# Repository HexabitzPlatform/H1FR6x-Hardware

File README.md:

# H1FR6x-Hardware

Hexabitz TESEO-LIV4F GNSS Module Hardware Design

Redesign using the STM32G0B1CEU6 MCU and Teseo-LIV4F. Review the previous design for errors and correct them. Use the X-NUCLEO-LIV4A1 design as a reference.

This design must use two hexagons with a 4-layer PCB stack-up.

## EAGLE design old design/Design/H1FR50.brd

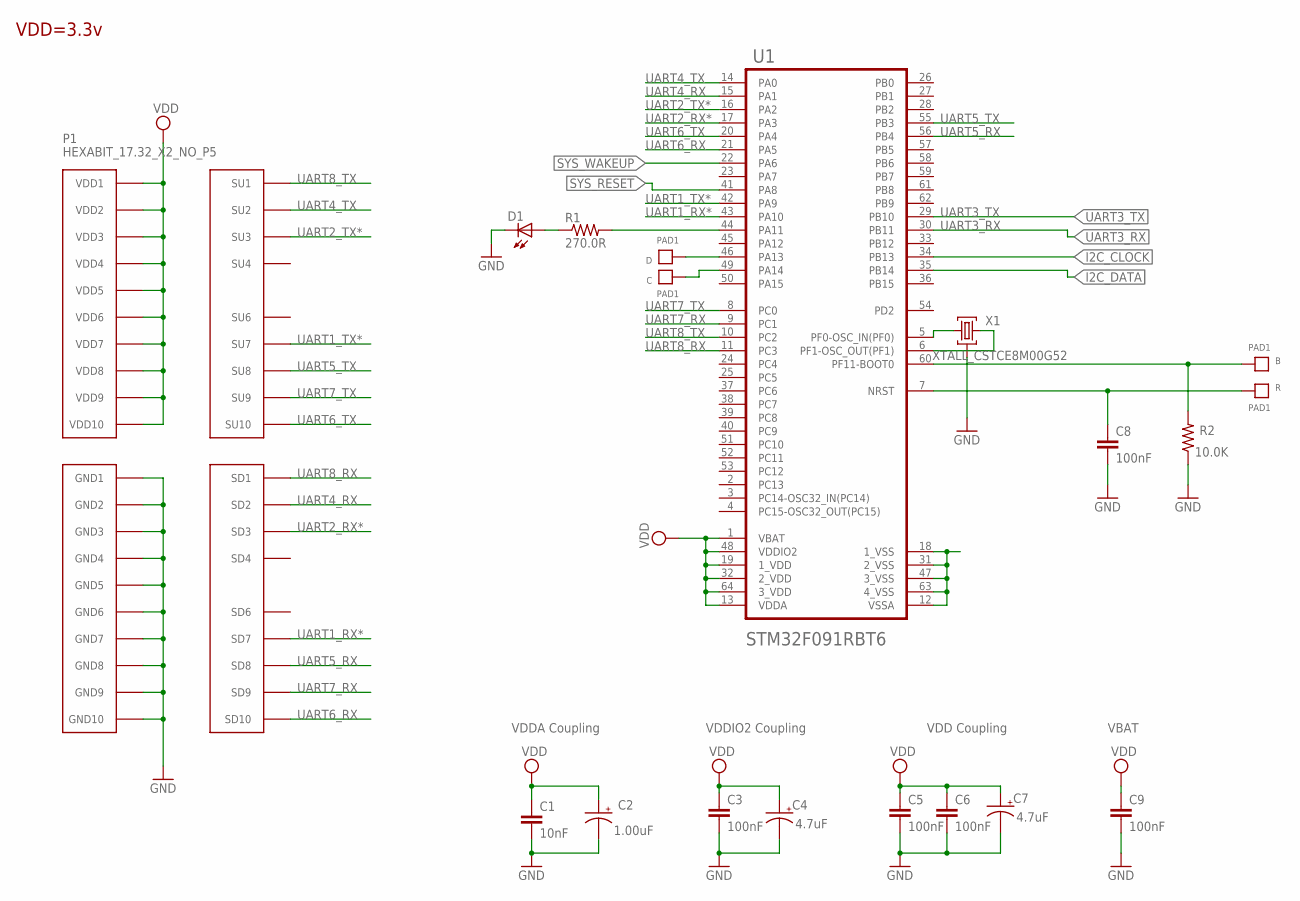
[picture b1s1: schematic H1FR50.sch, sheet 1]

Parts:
B: PAD1
C: PAD1
C1: 10nF; C-0603; TOLERANCE 10%; VOLTAGE_RATING 50V; MPN C0603C103K5RACTU
C2: 1.00uF; C-0805-POL; TOLERANCE 10%; VOLTAGE_RATING 16V; MPN CC0805KKX7R7BB105
C3, C6, C8: 100nF; C-0603; TOLERANCE 10%; VOLTAGE_RATING 10V; MPN C0603C104K8RACTU
C4, C7: 4.7uF; C-0805-POL; TOLERANCE 10%; VOLTAGE_RATING 25V; MPN GRM21BC81E475KA12L
C5: 100nF; C-0603; TOLERANCE 10%; VOLTAGE_RATING 10; MPN C0603C104K8RACTU
C9: 100nF; C-0603; TOLERANCE 10V; VOLTAGE_RATING 10%; MPN C0603C104K8RACTU
D: PAD1
D1: VLMS1300-GS08; MPN VLMS1300-GS08
P1: HEXABIT_17.32_X2_NO_P5
R: PAD1
R1: 270.0R; R-0603; TOLERANCE 1%; MPN RC0603FR-07270RL
R2: 10.0K; R-0603; TOLERANCE 5%; MPN RC0603JR-0710KL
U1: STM32F091RBT6STMICROELECTRONICS_STM32F091RBT6_0_1; STMICROELECTRONICS_STM32F091RBT6_1
X1: XTALL_CSTCE8M00G52

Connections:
B1: B.P$1, B.P$2, R2.2, U1.60 (PF11-BOOT0)
GND: C1.2, C2.2 (-), C3.2, C4.2 (-), C5.2, C6.2, C7.2 (-), C8.2, C9.2, D1.C, P1.PAD_PD11 (GND1), P1.PAD_PD12 (GND2), P1.PAD_PD13 (GND3), P1.PAD_PD14 (GND4), P1.PAD_PD15 (GND5), P1.PAD_PD16 (GND6), P1.PAD_PD17 (GND7), P1.PAD_PD18 (GND8), P1.PAD_PD19 (GND9), P1.PAD_PD20 (GND10), R2.1, U1.12 (VSSA), U1.18 (1_VSS), U1.31 (2_VSS), U1.47 (3_VSS), U1.63 (4_VSS), X1.P$2 (2); also elsewhere on the board
I2C_CLOCK: U1.34 (PB13); also elsewhere on the board
I2C_DATA: U1.35 (PB14); also elsewhere on the board
unnamed: D1.A, R1.1
unnamed: U1.5 (PF0-OSC_IN(PF0)), X1.P$1 (1)
unnamed: U1.6 (PF1-OSC_OUT(PF1)), X1.P$3 (3)
unnamed: D.P$1, D.P$2, U1.46 (PA13)
unnamed: C.P$1, C.P$2, U1.49 (PA14)
unnamed: R1.2, U1.44 (PA11)
R1: C8.1, R.P$1, R.P$2, U1.7 (NRST)
SYS_RESET: U1.41 (PA8); also elsewhere on the board
SYS_WAKEUP: U1.22 (PA6); also elsewhere on the board
UART1_RX*: P1.PAD_PD7 (SD7), U1.43 (PA10)
UART1_TX*: P1.PAD_PU7 (SU7), U1.42 (PA9)
UART2_RX*: P1.PAD_PD3 (SD3), U1.17 (PA3)
UART2_TX*: P1.PAD_PU3 (SU3), U1.16 (PA2)
UART3_RX: U1.30 (PB11); also elsewhere on the board
UART3_TX: U1.29 (PB10); also elsewhere on the board
UART4_RX: P1.PAD_PD2 (SD2), U1.15 (PA1)
UART4_TX: P1.PAD_PU2 (SU2), U1.14 (PA0)
UART5_RX: P1.PAD_PD8 (SD8), U1.56 (PB4)
UART5_TX: P1.PAD_PU8 (SU8), U1.55 (PB3)
UART6_RX: P1.PAD_PD10 (SD10), U1.21 (PA5)
UART6_TX: P1.PAD_PU10 (SU10), U1.20 (PA4)
UART7_RX: P1.PAD_PD9 (SD9), U1.9 (PC1)
UART7_TX: P1.PAD_PU9 (SU9), U1.8 (PC0)
UART8_RX: P1.PAD_PD1 (SD1), U1.11 (PC3)
UART8_TX: P1.PAD_PU1 (SU1), U1.10 (PC2)
VDD: C1.1, C2.1 (+), C3.1, C4.1 (+), C5.1, C6.1, C7.1 (+), C9.1, P1.PAD_PU11 (VDD1), P1.PAD_PU12 (VDD2), P1.PAD_PU13 (VDD3), P1.PAD_PU14 (VDD4), P1.PAD_PU15 (VDD5), P1.PAD_PU16 (VDD6), P1.PAD_PU17 (VDD7), P1.PAD_PU18 (VDD8), P1.PAD_PU19 (VDD9), P1.PAD_PU20 (VDD10), U1.1 (VBAT), U1.13 (VDDA), U1.19 (1_VDD), U1.32 (2_VDD), U1.48 (VDDIO2), U1.64 (3_VDD); also elsewhere on the board

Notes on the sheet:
VDDA Coupling
VDDIO2 Coupling
VDD Coupling
VBAT
VDD=3.3v

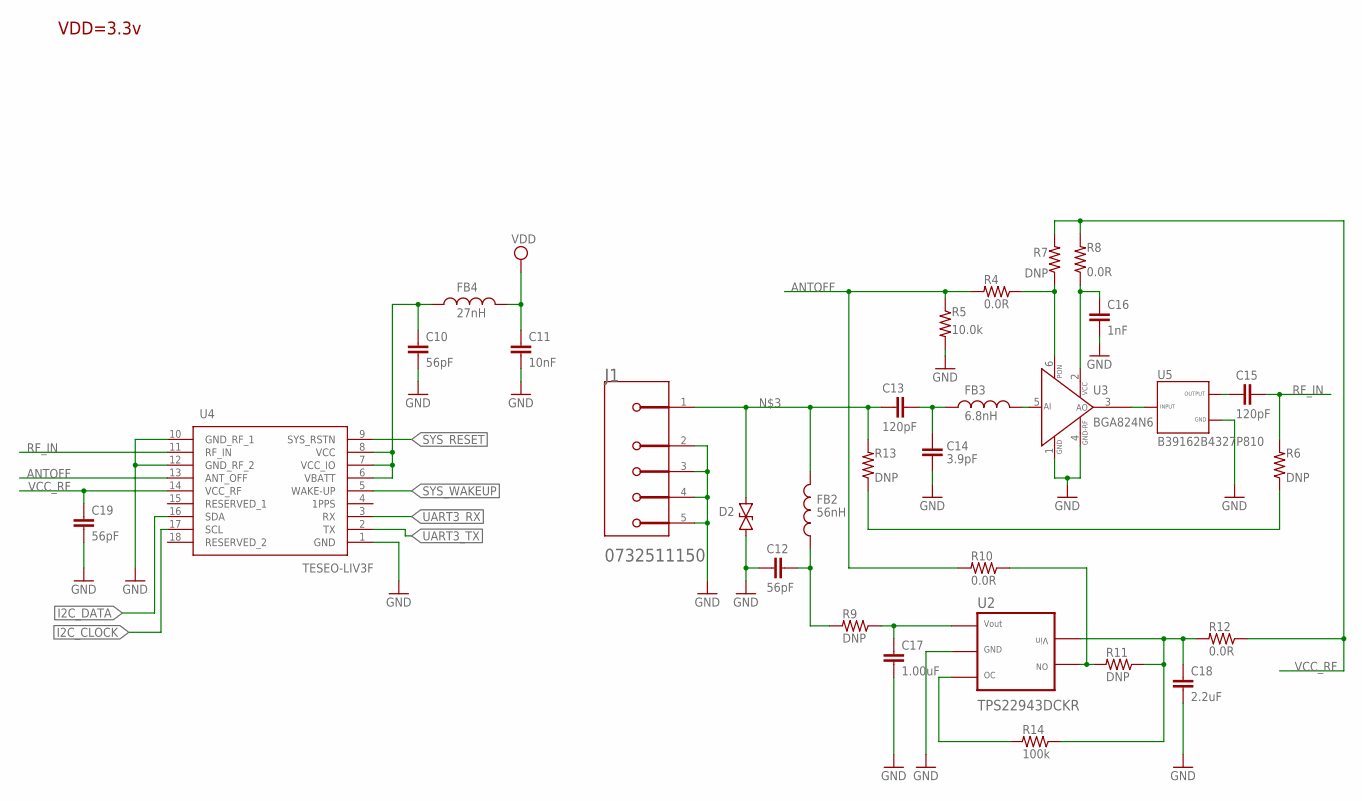
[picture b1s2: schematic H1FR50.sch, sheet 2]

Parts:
C10, C19: 56pF; C-0201; MPN GRM0335C1E560GA01D
C11: 10nF; C-0402; MPN CGA2B3X7R1H103K050BE
C12: 56pF; C-0402; MPN GRM1555C1H560JA01D
C13, C15: 120pF; C-0402; MPN GRM1555C1H121JA01D
C14: 3.9pF; C-0402; MPN GRM1555C1H3R9WA01D
C16: 1nF; C-0402; MPN GRM155R71H102KA01D
C17: 1.00uF; C-0402; MPN C0402C105K8PAC7411
C18: 2.2uF; C-0402; MPN C0402C225K7PACTU
D2: ESDARF02-1BU2CK; CAPC0201X13N
FB2: 56nH; FB-0402; MPN LQW15AN6N8G00D
FB3: 6.8nH; FB-0402; MPN 744784156A
FB4: 27nH; FB-0402; MPN LQG15HS27NJ02D
J1: MOLEX_INC_0732511150MOLEX_INC_0732511150_0_0; MOLEX_INC_0732511150_0
R4, R8, R10, R12: 0.0R; R-0402
R5: 10.0k; R-0402; TOLERANCE ±1%; MPN CRGCQ0402F10K
R6, R7, R9, R11, R13: DNP; R-0402
R14: 100k; R-0603; TOLERANCE ±1%; MPN AC0603FR-07100KL
U2: TPS22943DCKR; SOT65P210X110-5N
U3: BGA824N6
U4: TESEO-LIV3F; SON110P970X1010X230-18N
U5: B39162B4327P810; FIL_B39162B4327P810

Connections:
ANTOFF: R4.2, R5.1, R10.2, U4.13 (ANT_OFF)
ANT_IN: R6.1, R13.1
GND: C10.1, C11.1, C12.1, C14.1, C16.2, C17.2, C18.2, C19.1, D2.1, J1.2 (MNT_1), J1.3 (MNT_2), J1.4 (MNT_3), J1.5 (MNT_4), R5.2, U2.2 (GND), U3.1 (GND), U3.4 (GND-RF), U4.1 (GND), U4.10 (GND_RF_1), U4.12 (GND_RF_2), U5.2 (GND), U5.3 (GND), U5.5 (GND); also elsewhere on the board
I2C_CLOCK: U4.17 (SCL); also elsewhere on the board
I2C_DATA: U4.16 (SDA); also elsewhere on the board
unnamed: C13.2, C14.2, FB3.1
unnamed: R14.2, U2.3 (OC)
unnamed: C13.1, D2.2, FB2.2, J1.1, R13.2
unnamed: C12.2, FB2.1, R9.2
unnamed: FB3.2, U3.5 (AI)
unnamed: U3.3 (AO), U5.1 (INPUT)
unnamed: R4.1, R7.1, U3.6 (PON)
unnamed: C15.1, U5.4 (OUTPUT)
unnamed: C16.1, R8.1, U3.2 (VCC)
unnamed: C17.1, R9.1, U2.1 (VOUT)
unnamed: R10.1, R11.2, U2.4 (ON)
unnamed: C18.1, R11.1, R12.2, R14.1, U2.5 (VIN)
RF_IN: C15.2, R6.2, U4.11 (RF_IN)
SYS_RESET: U4.9 (SYS_RSTN); also elsewhere on the board
SYS_WAKEUP: U4.5 (WAKE-UP); also elsewhere on the board
UART3_RX: U4.3 (RX); also elsewhere on the board
UART3_TX: U4.2 (TX); also elsewhere on the board
VCC_RF: C19.2, R7.2, R8.2, R12.1, U4.14 (VCC_RF)
VCC_RF1: C10.2, FB4.1, U4.6 (VBATT), U4.7 (VCC_IO), U4.8 (VCC)
VDD: C11.2, FB4.2; also elsewhere on the board

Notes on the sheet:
VDD=3.3v

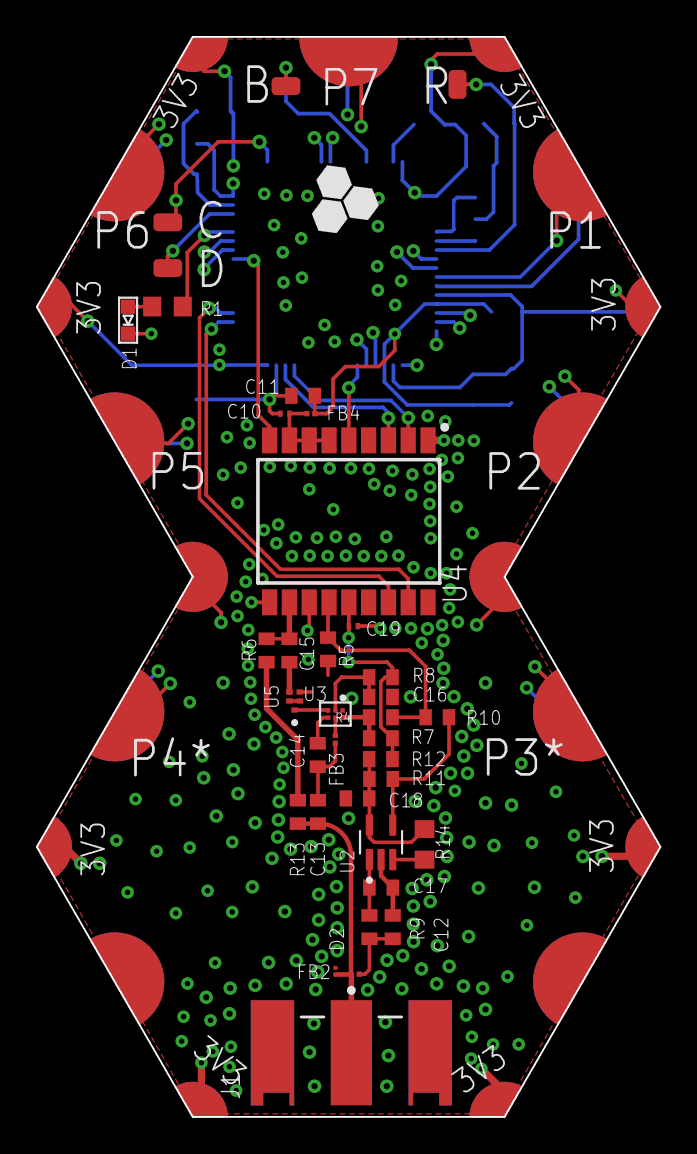
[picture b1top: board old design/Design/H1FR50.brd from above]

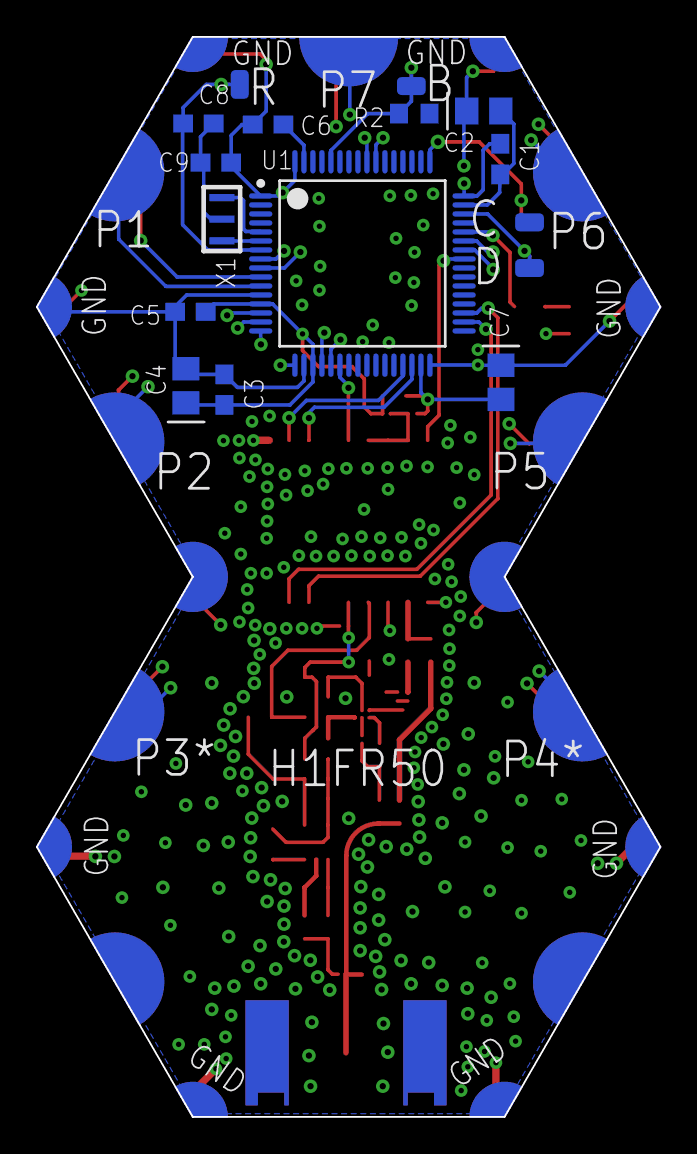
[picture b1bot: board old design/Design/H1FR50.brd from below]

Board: 4 copper layers, 34.6 x 60.0 mm, 49 parts (12 on the bottom side), 47 nets.

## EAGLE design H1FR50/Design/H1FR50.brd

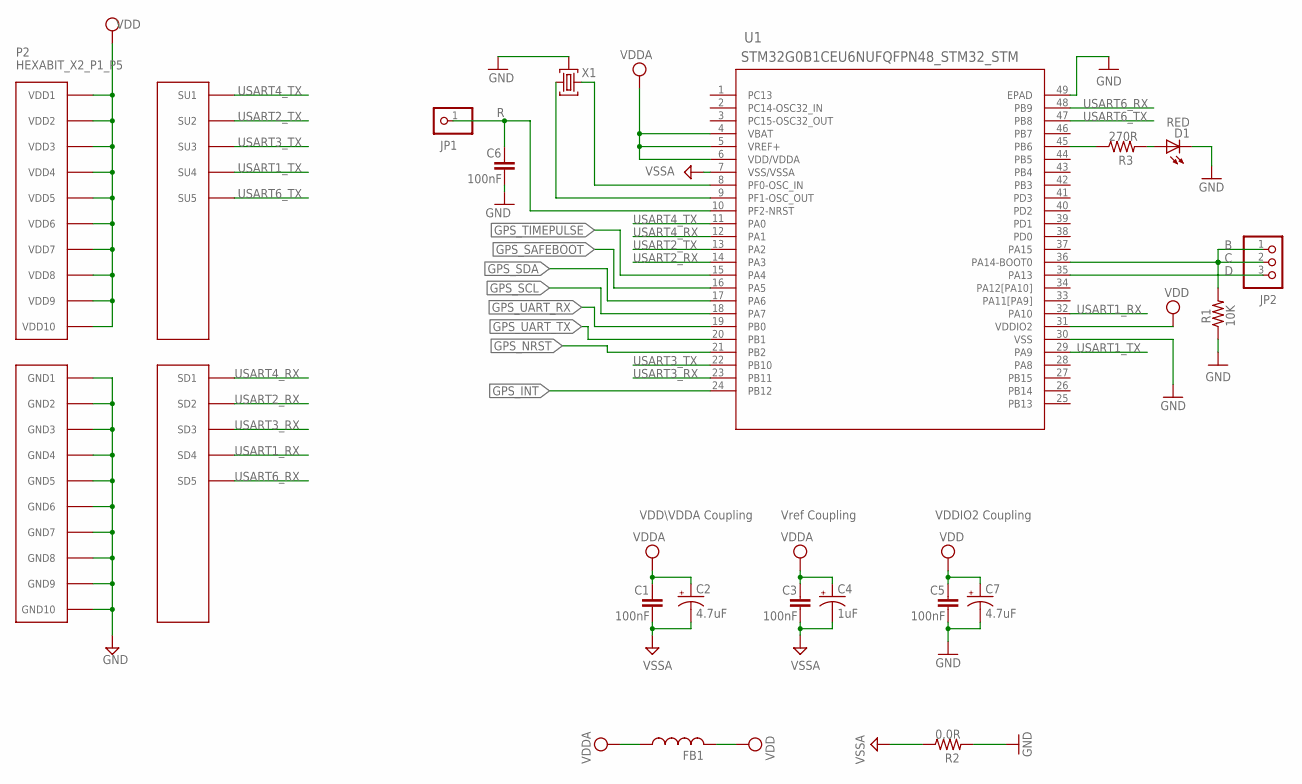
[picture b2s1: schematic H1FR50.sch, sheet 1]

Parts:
C1, C3, C5, C6: 100nF; C-0603
C2, C7: 4.7uF; C-0805-POL
C4: 1uF; C-0805-POL
D1: RED; VLMS1300-GS08
FB1: FB-0603
JP1: R; 1X01
JP2: PINHD-1X3; 1X03
P2: HEXABIT_X2_P1_P5; HEXABIT_17.32_X2_P1_P5
R1: 10K; R-0603
R2: 0.0R; R-0603
R3: 270R; R-0603
U1: STM32G0B1CEU6NUFQFPN48_STM32_STM; UFQFPN48_STM32_STM
X1: XTALL_CSTCE8M00G52

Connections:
C: JP2.1, JP2.2, R1.2, U1.36 (PA14-BOOT0)
D: JP2.3, U1.35 (PA13)
GND: C5.2, C6.2, C7.2 (-), D1.C, P2.PAD_PD11 (GND1), P2.PAD_PD12 (GND2), P2.PAD_PD13 (GND3), P2.PAD_PD14 (GND4), P2.PAD_PD15 (GND5), P2.PAD_PD16 (GND6), P2.PAD_PD17 (GND7), P2.PAD_PD18 (GND8), P2.PAD_PD19 (GND9), P2.PAD_PD20 (GND10), R1.1, R2.2, U1.30 (VSS), U1.49 (EPAD), X1.P$2 (2); also elsewhere on the board
GPS_INT: U1.24 (PB12); also elsewhere on the board
GPS_NRST: U1.21 (PB2); also elsewhere on the board
GPS_SAFEBOOT: U1.16 (PA5); also elsewhere on the board
GPS_SCL: U1.18 (PA7); also elsewhere on the board
GPS_SDA: U1.17 (PA6); also elsewhere on the board
GPS_TIMEPULSE: U1.15 (PA4); also elsewhere on the board
GPS_UART_RX: U1.19 (PB0); also elsewhere on the board
GPS_UART_TX: U1.20 (PB1); also elsewhere on the board
unnamed: D1.A, R3.2
unnamed: U1.8 (PF0-OSC_IN), X1.P$1 (1)
unnamed: U1.9 (PF1-OSC_OUT), X1.P$3 (3)
unnamed: C6.1, JP1.1, U1.10 (PF2-NRST)
unnamed: R3.1, U1.45 (PB6)
USART1_RX: P2.PAD_PD4 (SD4), U1.32 (PA10)
USART1_TX: P2.PAD_PU4 (SU4), U1.29 (PA9)
USART2_RX: P2.PAD_PD2 (SD2), U1.14 (PA3)
USART2_TX: P2.PAD_PU2 (SU2), U1.13 (PA2)
USART3_RX: P2.PAD_PD3 (SD3), U1.23 (PB11)
USART3_TX: P2.PAD_PU3 (SU3), U1.22 (PB10)
USART4_RX: P2.PAD_PD1 (SD1), U1.12 (PA1)
USART4_TX: P2.PAD_PU1 (SU1), U1.11 (PA0)
USART6_RX: P2.PAD_PD5 (SD5), U1.48 (PB9)
USART6_TX: P2.PAD_PU5 (SU5), U1.47 (PB8)
VDD: C5.1, C7.1 (+), FB1.2, P2.PAD_PU11 (VDD1), P2.PAD_PU12 (VDD2), P2.PAD_PU13 (VDD3), P2.PAD_PU14 (VDD4), P2.PAD_PU15 (VDD5), P2.PAD_PU16 (VDD6), P2.PAD_PU17 (VDD7), P2.PAD_PU18 (VDD8), P2.PAD_PU19 (VDD9), P2.PAD_PU20 (VDD10), U1.31 (VDDIO2); also elsewhere on the board
VDDA: C1.1, C2.1 (+), C3.1, C4.1 (+), FB1.1, U1.4 (VBAT), U1.5 (VREF+), U1.6 (VDD/VDDA)
VSSA: C1.2, C2.2 (-), C3.2, C4.2 (-), R2.1, U1.7 (VSS/VSSA)

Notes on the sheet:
Vref Coupling
VDDIO2 Coupling
VDD\VDDA Coupling

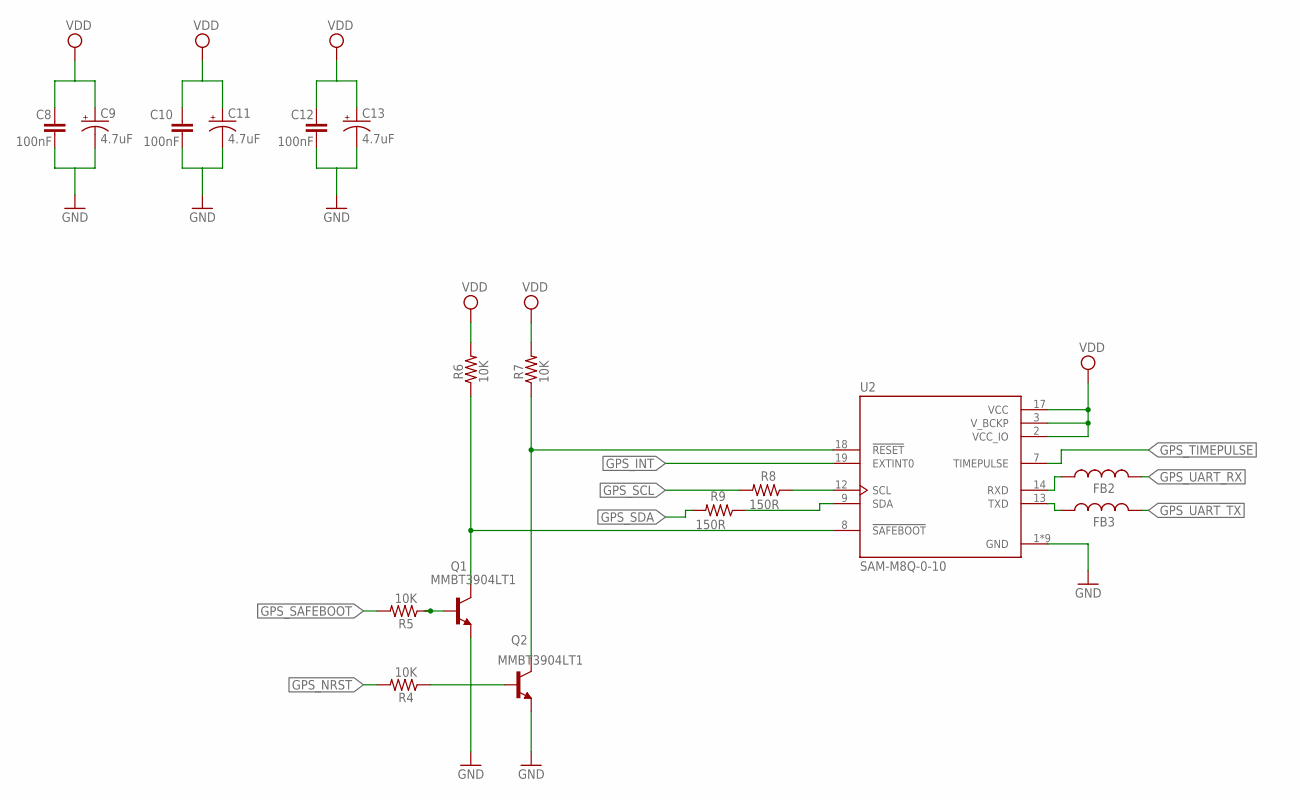
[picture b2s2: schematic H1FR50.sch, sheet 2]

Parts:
C8, C10, C12: 100nF; C-0603
C9, C11, C13: 4.7uF; C-0805-POL
FB2, FB3: BLM18KG601SN1D; FB-0603
Q1, Q2: MMBT3904LT1
R4, R5, R6, R7: 10K; R-0603
R8, R9: 150R; R-0603; MPN CRCW0603150RFKEA
U2: SAM-M8Q-0-10; MODULE_SAM-M8Q-0-10

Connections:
GND: C8.2, C9.2 (-), C10.2, C11.2 (-), C12.2, C13.2 (-), Q1.2 (E), Q2.2 (E), U2.1 (GND), U2.4 (GND), U2.5 (GND), U2.6 (GND), U2.10 (GND), U2.11 (GND), U2.15 (GND), U2.16 (GND), U2.20 (GND); also elsewhere on the board
GPS_INT: U2.19 (EXTINT0); also elsewhere on the board
GPS_NRST: R4.2; also elsewhere on the board
GPS_SAFEBOOT: R5.2; also elsewhere on the board
GPS_SCL: R8.2; also elsewhere on the board
GPS_SDA: R9.2; also elsewhere on the board
GPS_TIMEPULSE: U2.7 (TIMEPULSE); also elsewhere on the board
GPS_UART_RX: FB2.2; also elsewhere on the board
GPS_UART_TX: FB3.2; also elsewhere on the board
unnamed: Q2.3 (C), R7.1, U2.18 (!RESET)
unnamed: Q1.3 (C), R6.1, U2.8 (!SAFEBOOT)
unnamed: Q2.1 (B), R4.1
unnamed: Q1.1 (B), R5.1
unnamed: FB2.1, U2.14 (RXD)
unnamed: FB3.1, U2.13 (TXD)
unnamed: R8.1, U2.12 (SCL)
unnamed: R9.1, U2.9 (SDA)
VDD: C8.1, C9.1 (+), C10.1, C11.1 (+), C12.1, C13.1 (+), R6.2, R7.2, U2.2 (VCC_IO), U2.3 (V_BCKP), U2.17 (VCC); also elsewhere on the board

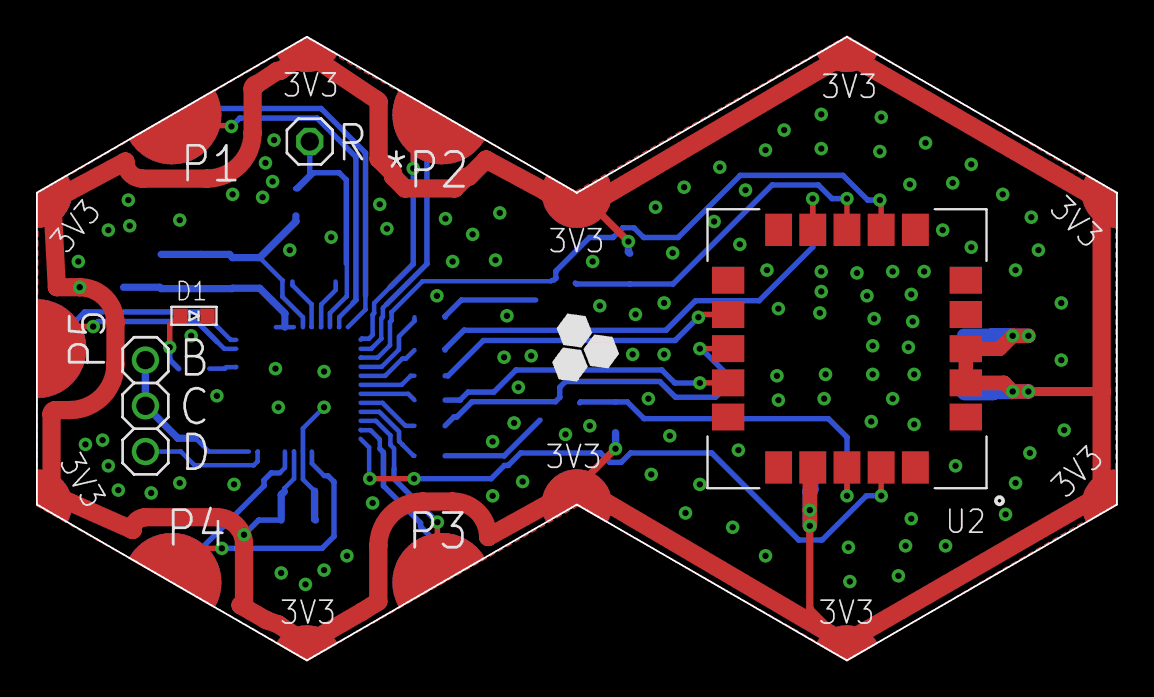
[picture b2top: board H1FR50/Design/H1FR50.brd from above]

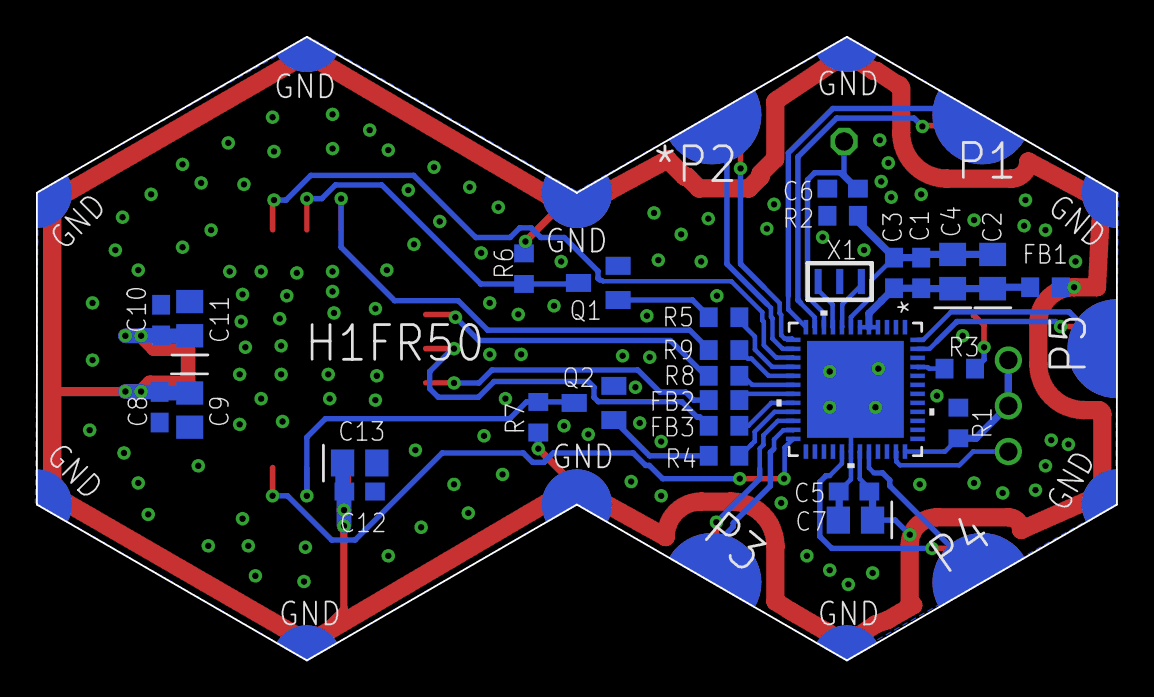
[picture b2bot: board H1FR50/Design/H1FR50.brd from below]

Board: 2 copper layers, 60.0 x 34.6 mm, 34 parts (29 on the bottom side), 37 nets.

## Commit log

2021-03-17 - Schematic - PCB - BOM - Documentation
2021-03-18 Added Keepout areas in PCB..
2021-03-19 - Rearanged all P#.. - Removed Keepout areas.. - Renamed all NM to DNP.. - Moved D1 from layer 16 to layer 1.. - Changed R8 from 0R NM to 0R.. - Placed more Grounding vias around RF connector in brd.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
2021-03-27 - Redesigned both Schematic and PCB.. - Updated BOM and Documentation..
2021-04-03 - Changed Polygen for layer 1 to GND - Wrote board specification on documentation layer
2021-04-05 Removed all Blined Vias..
2021-04-05 - Changed RF Connector.. - Documents and BOM were updated..
2021-04-07 - Changed the RF route width to 10 mil
2021-04-07 - Fixed some DRC errors.. - Changed TOP layer (1) polygon isolation to 7 mill
2021-04-17 - reconnected side pads to power..
2021-04-21 Updated BOM..
2021-04-22 - Updated BOM..
2022-09-12 -Changing the MC to STM32G0B1CEU6N -Changing the GPS Module to SAM-M8Q-0-10 u-blox
2022-09-24 -Changing the layout design to improve the performance
2023-02-13 -Correcting some documentaion issues
2025-10-16 The Altium template has been added.

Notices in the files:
parts and their libraries:
COPYRIGHT: Copyright (C) 2022 Ultra Librarian. All rights reserved.
